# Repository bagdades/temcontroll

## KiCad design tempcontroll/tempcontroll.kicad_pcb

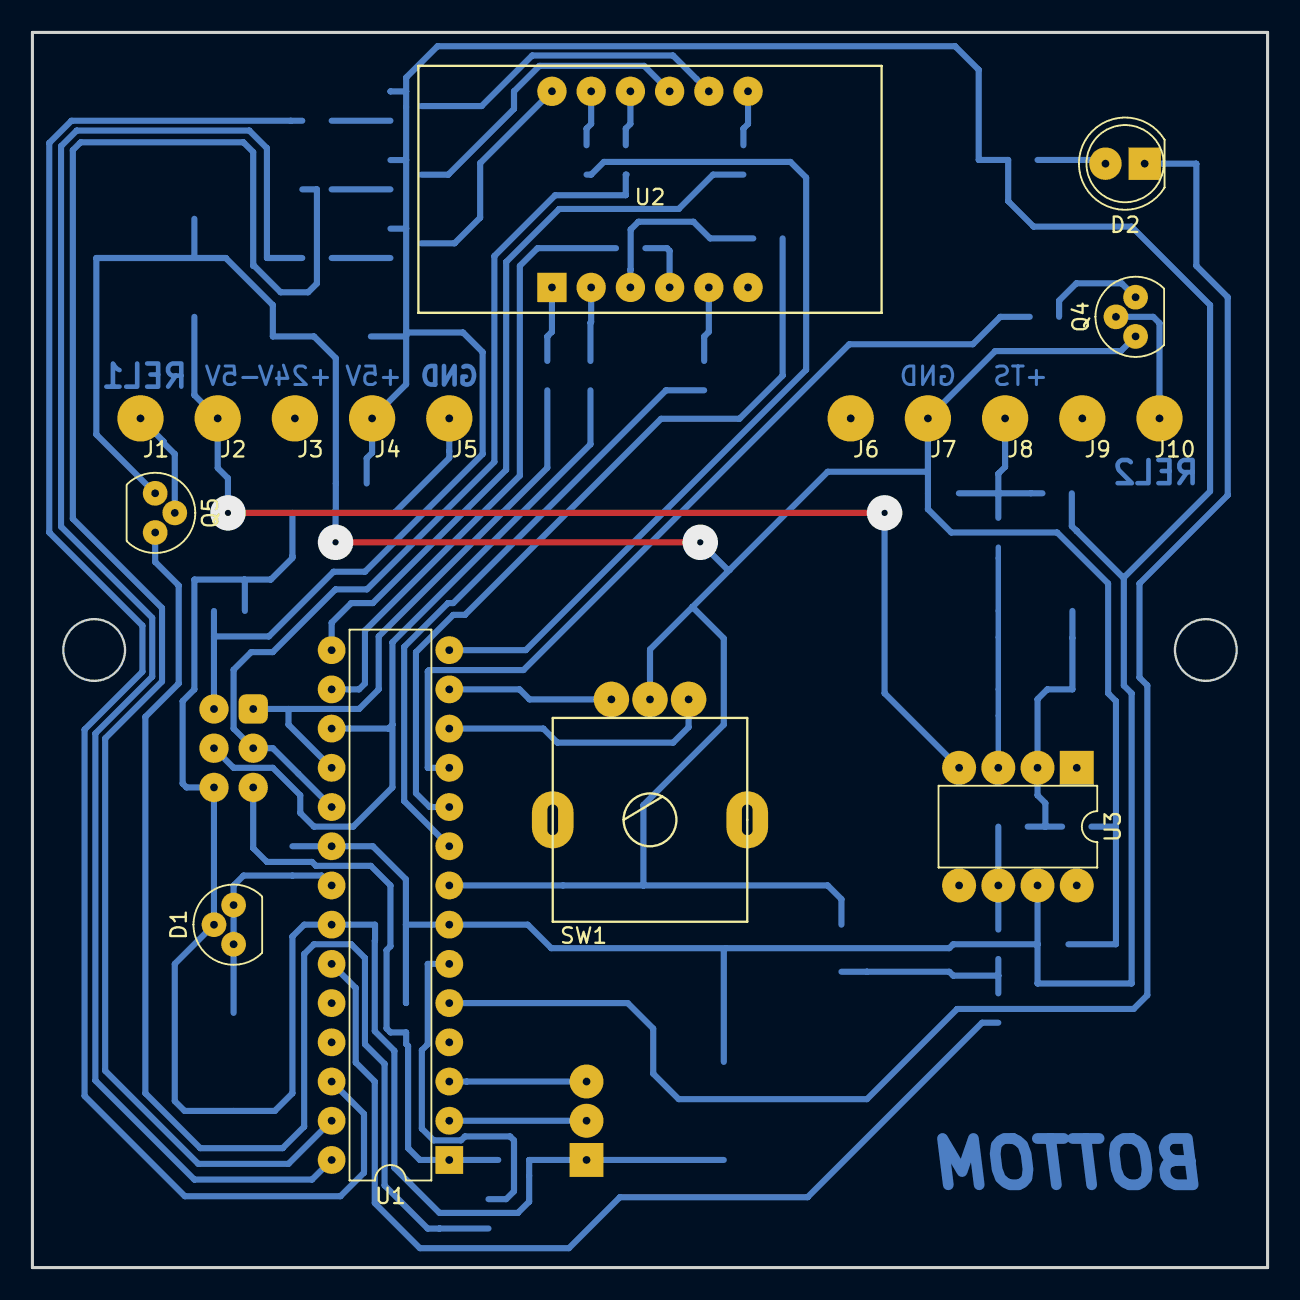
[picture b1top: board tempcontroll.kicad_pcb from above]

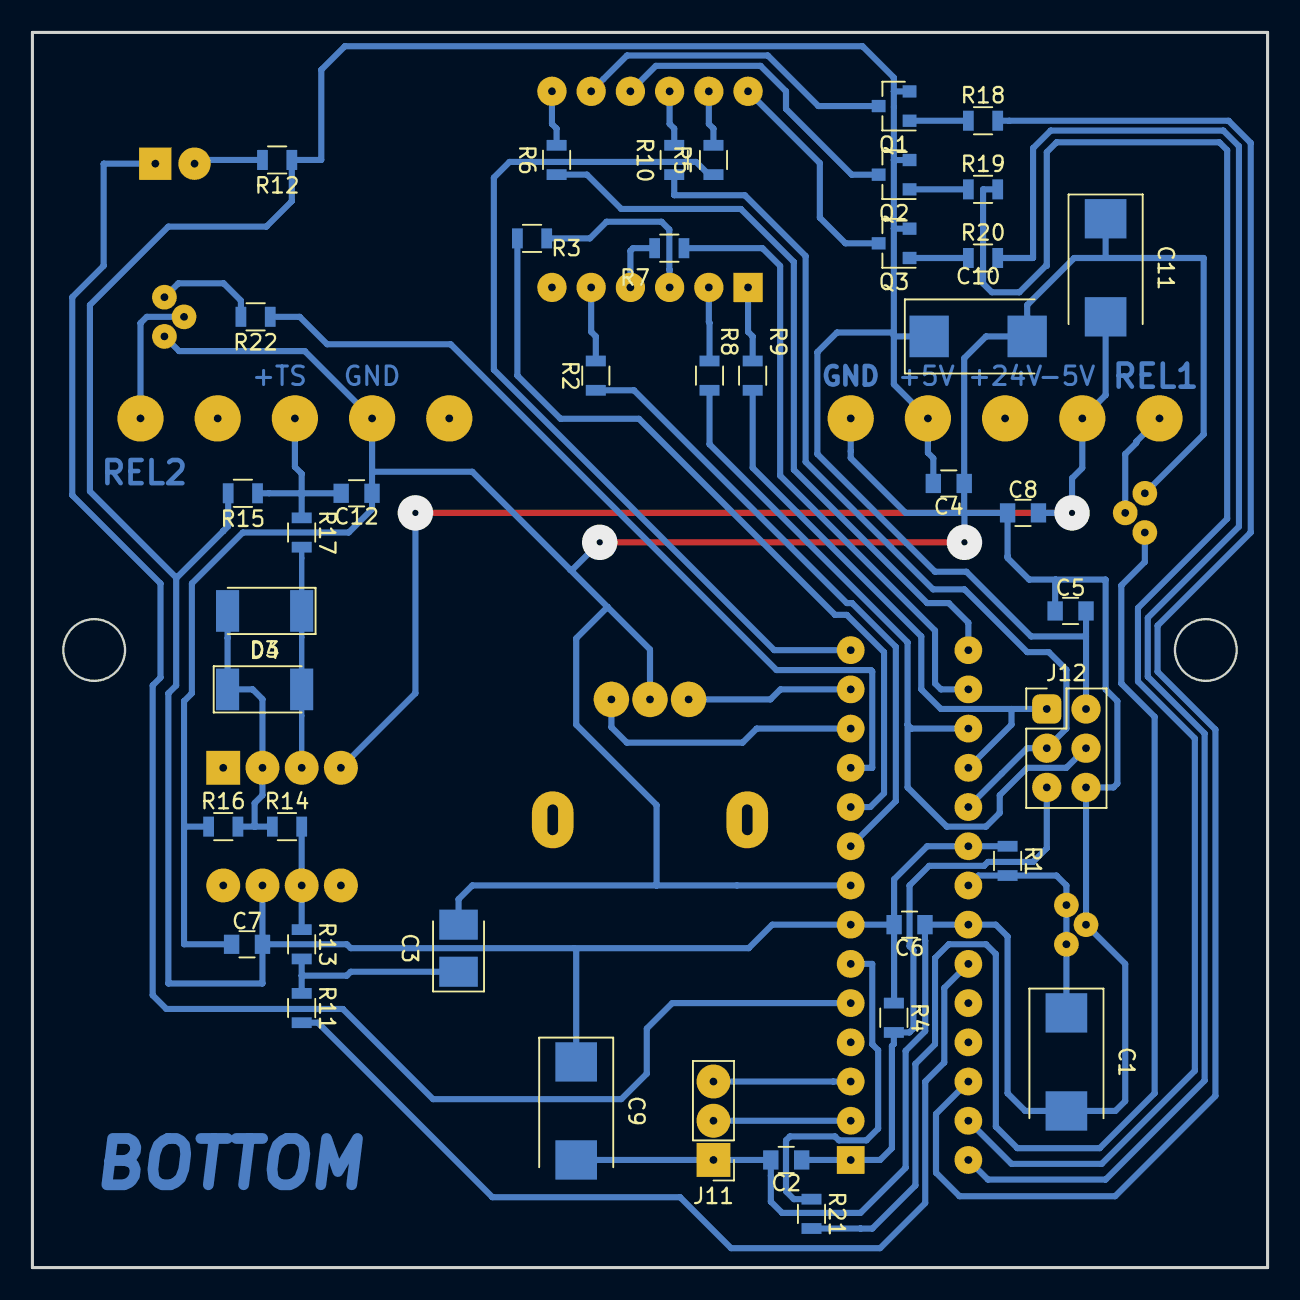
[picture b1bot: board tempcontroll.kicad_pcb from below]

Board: 2 copper layers, 80.0 x 80.0 mm, 59 parts (41 on the bottom side), 48 nets.

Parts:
C1, C9, C10, C11: 47u; CP_Tantalum_Case-D_EIA-7343-31_Reflow
C2, C4, C5, C6, C7: 100u; C_0805
C3: 1u; CP_Tantalum_Case-T_EIA-3528-12_Reflow
C8, C12: 100n; C_0805
D1: TL431LP; TO-92_Molded_Narrow
D2: LED; LED_D5.0mm
D3, D4: D; D_MELF
J1: REL1; PAD
J2: -5V; PAD
J3: +24V; PAD
J4: +5V; PAD
J5: GND; PAD
J6: +D; PAD
J7: -TS; PAD
J8: +TS; PAD
J9: REL2A; PAD
J10: REL2B; PAD
J11: Conn_01x03; Pin_Header_Straight_1x03_Pitch2.54mm
J12: AVR_SPI; Pin_Header_Straight_2x03_Pitch2.54mm
Q1, Q2, Q3: BC807; SOT-23
Q4, Q5: 2SD667; TO-92_Molded_Narrow
R1: 2k; R_0805
R2, R3, R5, R6, R7, R8, R9, R10: 220; R_0805
R4, R11, R13: 10k; R_0805
R12: 330; R_0805
R14: 22k; R_0805
R15: 6M8; R_0805
R16: 240; R_0805
R17: 470; R_0805
R18, R19, R20: 1k; R_0805
R21, R22: 4k7; R_0805
SW1: Rotary_Encoder; ENC1
U1: ATMEGA8-16PU; DIP-28_W7.62mm
U2: KL-4031-BSR; KL-4031
U3: OP07; DIP-8_W7.62mm

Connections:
+5V: C4.2, C5.2, C6.2, C7.2, C9.1, C10.1, J4.1, J12.2, Q1.2, Q2.2, Q3.2, R1.1, R4.1, R12.1, R15.2, U1.7, U1.20, U3.7
-5V: C8.2, C11.2, J2.1, U3.4
/A: R5.1, U2.11
/AREF: C1.1, D1.1, D1.3, R1.2, U1.21
/B: R6.1, U2.7
/C: R7.1, U2.4
/D: R8.1, U2.2
/D1: R18.2, U1.26
/D2: R19.2, U1.27
/D3: R20.2, U1.28
/DP: R3.2, U2.3
/E: R9.1, U2.1
/F: R10.1, U2.10
/G: R2.2, U2.5
/IN: D3.1, D4.2, R17.2, U3.3
/LED: D2.1, U1.5
/MISO: J12.1, R9.2, U1.18
/MOSI: J12.4, R8.2, U1.17
/REL1_O: R21.1, U1.6
/REL2_O: R22.1, U1.11
/RES: C2.1, J12.5, R4.2, U1.1
/RX: J11.2, U1.2
/SCK: J12.3, R10.2, U1.19
/TS: C12.2, J8.1, R15.1, R17.1
/TX: J11.3, U1.3
GND: C1.2, C2.2, C3.2, C4.1, C5.1, C6.1, C7.1, C8.1, C9.2, C10.2, C11.1, C12.1, D1.2, J5.1, J7.1, J11.1, J12.6, Q4.1, Q5.1, R16.1, SW1.2, U1.8, U1.22
unnamed: C3.1, R11.1, R13.2
unnamed: D2.2, R12.2
unnamed: D3.2, D4.1, R14.1, R16.2, U3.2
unnamed: J1.1, Q5.2
unnamed: J10.1, Q4.2
unnamed: Q1.1, R18.1
unnamed: Q1.3, U2.8
unnamed: Q2.1, R19.1
unnamed: Q2.3, U2.9
unnamed: Q3.1, R20.1
unnamed: Q3.3, U2.12
unnamed: Q4.3, R22.2
unnamed: Q5.3, R21.2
unnamed: R2.1, U1.9
unnamed: R3.1, U1.10
unnamed: R5.2, U1.14
unnamed: R6.2, U1.15
unnamed: R7.2, U1.16
unnamed: R11.2, U1.23
unnamed: R13.1, R14.2, U3.6
unnamed: SW1.1, U1.12
unnamed: SW1.3, U1.13

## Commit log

2017-12-19 Start work
2017-12-20 Job with pcb
2017-12-20 Finish work with pcb
2017-12-20 Start coding
2017-12-20 Start coding 2
2017-12-22 Prefinal work with pcb
2017-12-23 Work with code
2017-12-24 Final pcb
2017-12-24 Output pcb
2017-12-25 Solder pcb
2017-12-26 Start write soft
2017-12-29 Finish coding work of encoder
2018-01-01 Prefinish work
2018-01-01 Final
